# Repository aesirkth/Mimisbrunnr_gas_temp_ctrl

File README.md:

# Mimisbrunnr_gas_temp_ctrl

Mímisbrunnr gas tank temperature control unit

Project hierarchy: Mjölnir → Mimisbrunnr

## About

Mímisbrunnur is a temperature control unit that controls the temperature of the N<sub>2</sub> gas tank that is used as the oxidizer for the Mjölnir rocket.
The unit will regulate the temperature the desired temperature.
It will measure the temperature of the tank and then turn on a pump to allow warm water to flow in a tube around the tank.

## Requirements
1. Regulate the temperature of the oxidizer gas tank for the Mjölnir rocket
2. Manual as well as digital controls
    1. Manual control:
        1. Screen to see configurations
        2. Buttons to control
    2. Digital control:
        1. Connect through wifi and integrated into the system of Mjölnir
        2. Option to connect through CAN bus
3. Measure the temperature
    1. Have 3 temperature sensors: 1 top, 1 middle, 1 bottom
4. Turn a water pump to heat the tank
5. Tolerate rainy, snowy or other similar weather conditions

### Optional Requirements
1. Control heating element
2. Fully Waterproof

## Usage

Buttons to navigate

Connectors

## PCB

## Box

## Software

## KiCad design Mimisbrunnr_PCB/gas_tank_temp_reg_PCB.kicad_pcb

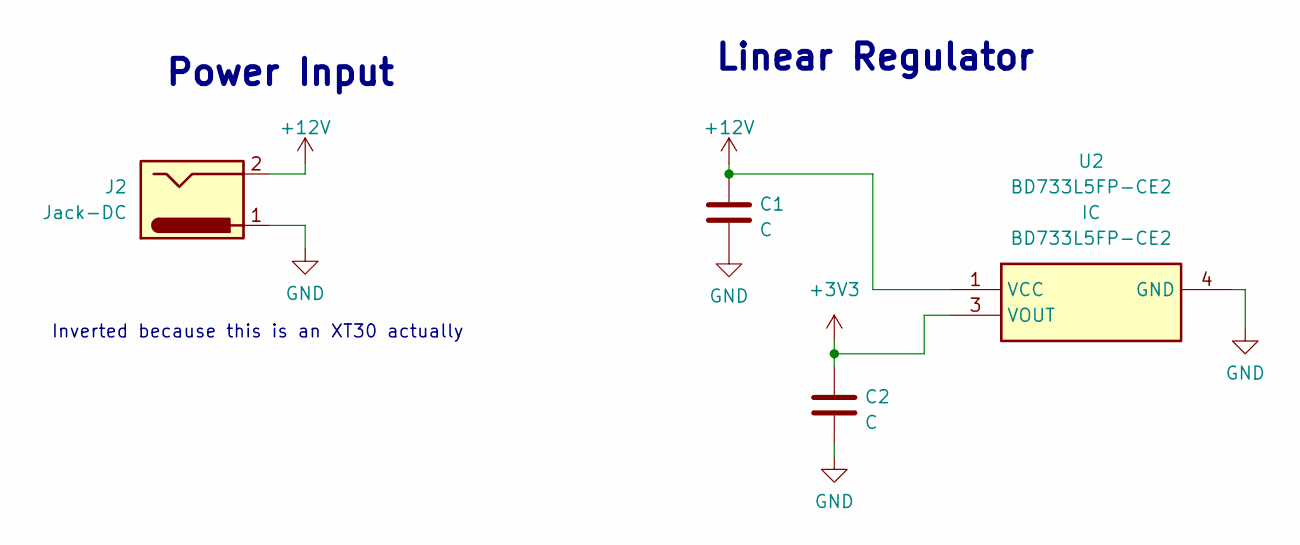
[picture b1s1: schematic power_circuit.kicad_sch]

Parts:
C1, C2: C; C_0805_2012Metric
J2: Jack-DC; AMASS_XT30PW-M_1x02_P2.50mm_Horizontal
U2: BD733L5FP-CE2; BD750L5FPCE2; Mouser Part Number 755-BD733L5FP-CE2

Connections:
+3.3V: C2.1, U2.3 (VOUT); also elsewhere on the board
+12V: C1.1, J2.2, U2.1 (VCC); also elsewhere on the board
GND: C1.2, C2.2, J2.1, U2.4 (GND); also elsewhere on the board

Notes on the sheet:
Power Input
Linear Regulator
Inverted because this is an XT30 actually

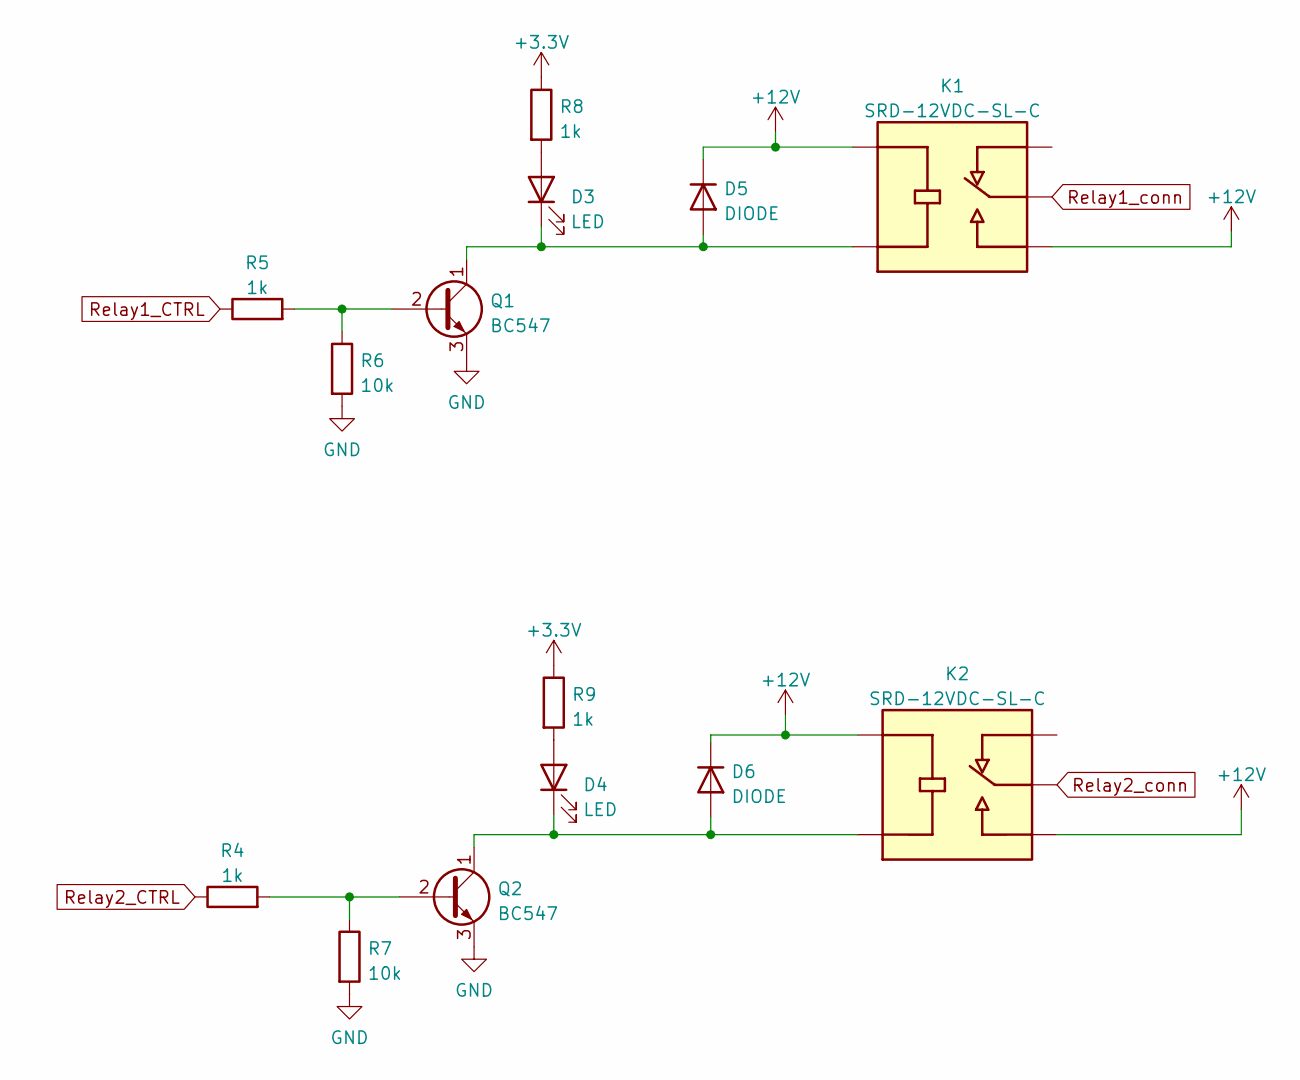
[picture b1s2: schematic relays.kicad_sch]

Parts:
D3, D4: LED; LED_0805_2012Metric
D5, D6: DIODE; D_0805_2012Metric
K1, K2: SRD-12VDC-SL-C; RELAY_SRD-12VDC-SL-C; PARTREV 1.0
Q1, Q2: BC547; TO-92_Inline
R4, R5, R8, R9: 1k; R_0805_2012Metric
R6, R7: 10k; R_0805_2012Metric

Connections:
+3.3V: R8.1, R9.1; also elsewhere on the board
+12V: D5.2 (K), D6.2 (K), K1.COIL1, K1.NO, K2.COIL1, K2.NO; also elsewhere on the board
GND: Q1.3 (E), Q2.3 (E), R6.2, R7.2; also elsewhere on the board
unnamed: D3.1 (K), D5.1 (A), K1.COIL2, Q1.1 (C)
unnamed: D3.2 (A), R8.2
unnamed: D4.1 (K), D6.1 (A), K2.COIL2, Q2.1 (C)
unnamed: D4.2 (A), R9.2
unnamed: Q1.2 (B), R5.2, R6.1
unnamed: Q2.2 (B), R4.2, R7.1
Relay1_CTRL: R5.1; also elsewhere on the board
Relay1_conn: K1.COM; also elsewhere on the board
Relay2_CTRL: R4.1; also elsewhere on the board
Relay2_conn: K2.COM; also elsewhere on the board

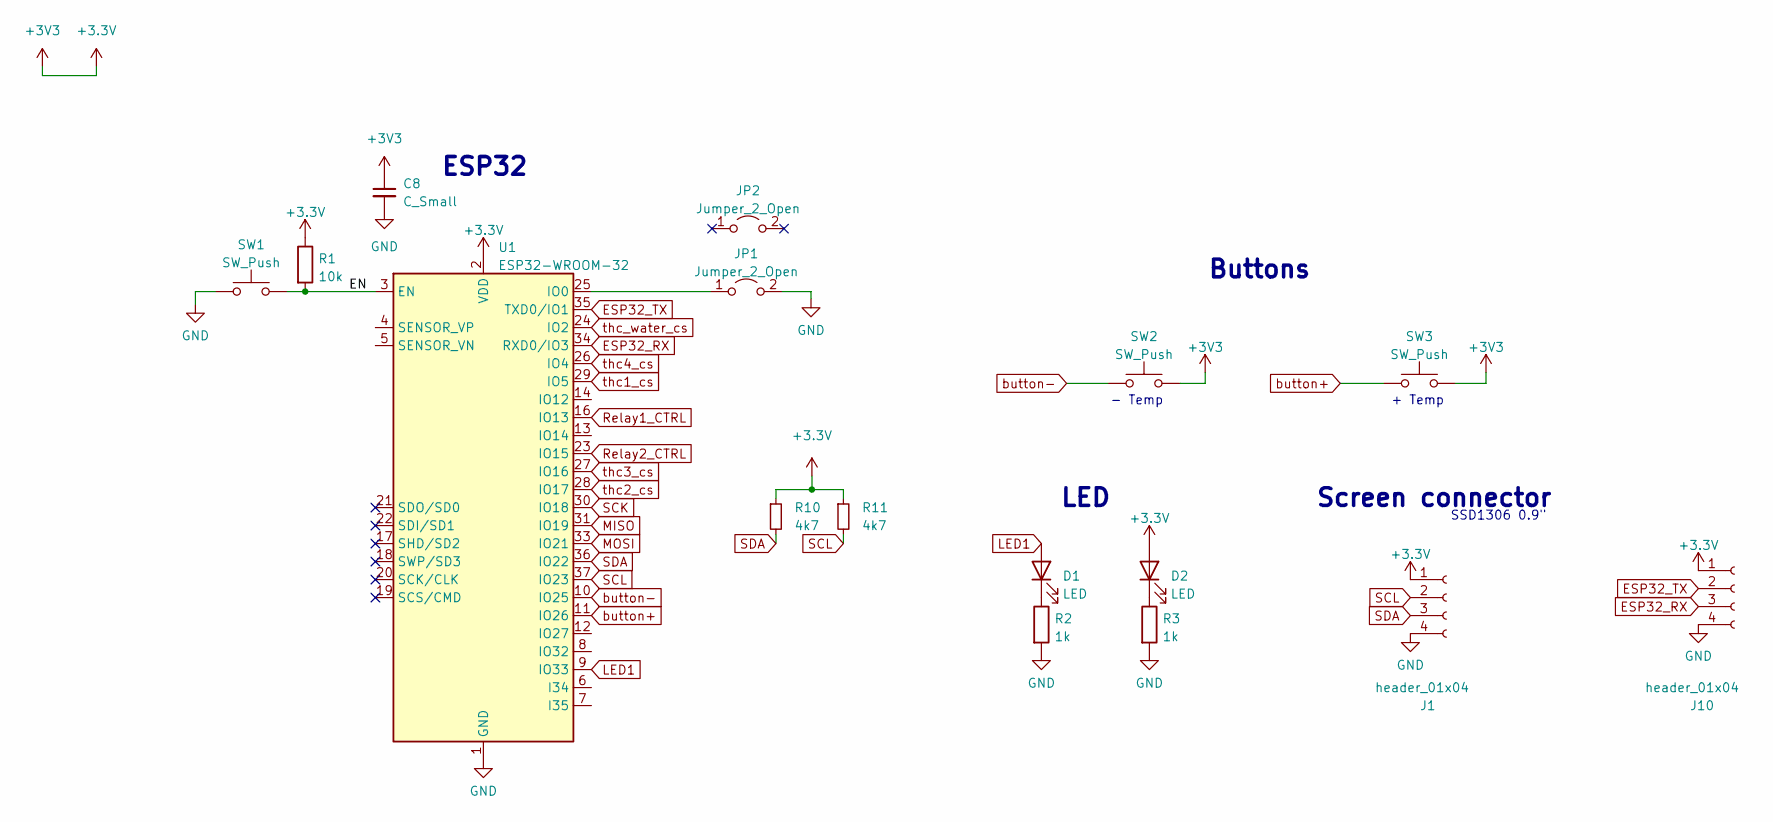
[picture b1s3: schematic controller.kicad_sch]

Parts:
C8: C_Small; C_0805_2012Metric
D1, D2: LED; LED_0805_2012Metric
J1, J10: header_01x04; PinHeader_1x04_P2.54mm_Vertical
JP1, JP2: Jumper_2_Open; PinHeader_1x02_P2.54mm_Vertical
R1: 10k; R_0805_2012Metric
R2, R3: 1k; R_0805_2012Metric
R10, R11: 4k7; R_0805_2012Metric
SW1, SW2, SW3: SW_Push; SW_SPST_B3U-1000P
U1: ESP32-WROOM-32

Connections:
+3.3V: C8.1, D2.2 (A), J1.1, J10.1, R1.1, R10.1, R11.1, SW2.2, SW3.2, U1.2 (VDD); also elsewhere on the board
/Controller/EN: R1.2, SW1.2, U1.3 (EN)
ESP32_RX: J10.3, U1.34 (RXD0/IO3)
ESP32_TX: J10.2, U1.35 (TXD0/IO1)
GND: C8.2, J1.4, J10.4, JP1.2 (B), R2.2, R3.2, SW1.1, U1.1 (GND), U1.15 (GND), U1.38 (GND), U1.39 (GND); also elsewhere on the board
LED1: D1.2 (A), U1.9 (IO33)
MISO: U1.31 (IO19); also elsewhere on the board
MOSI: U1.33 (IO21); also elsewhere on the board
unnamed: D1.1 (K), R2.1
unnamed: D2.1 (K), R3.1
unnamed: JP1.1 (A), U1.25 (IO0)
Relay1_CTRL: U1.16 (IO13); also elsewhere on the board
Relay2_CTRL: U1.23 (IO15); also elsewhere on the board
SCK: U1.30 (IO18); also elsewhere on the board
SCL: J1.2, R11.2, U1.37 (IO23)
SDA: J1.3, R10.2, U1.36 (IO22)
button+: SW3.1, U1.11 (IO26)
button-: SW2.1, U1.10 (IO25)
thc1_cs: U1.29 (IO5); also elsewhere on the board
thc2_cs: U1.28 (IO17); also elsewhere on the board
thc3_cs: U1.27 (IO16); also elsewhere on the board
thc4_cs: U1.26 (IO4); also elsewhere on the board
thc_water_cs: U1.24 (IO2); also elsewhere on the board

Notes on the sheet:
Buttons
Screen connector
+ Temp
ESP32
- Temp
LED
SSD1306 0.9"

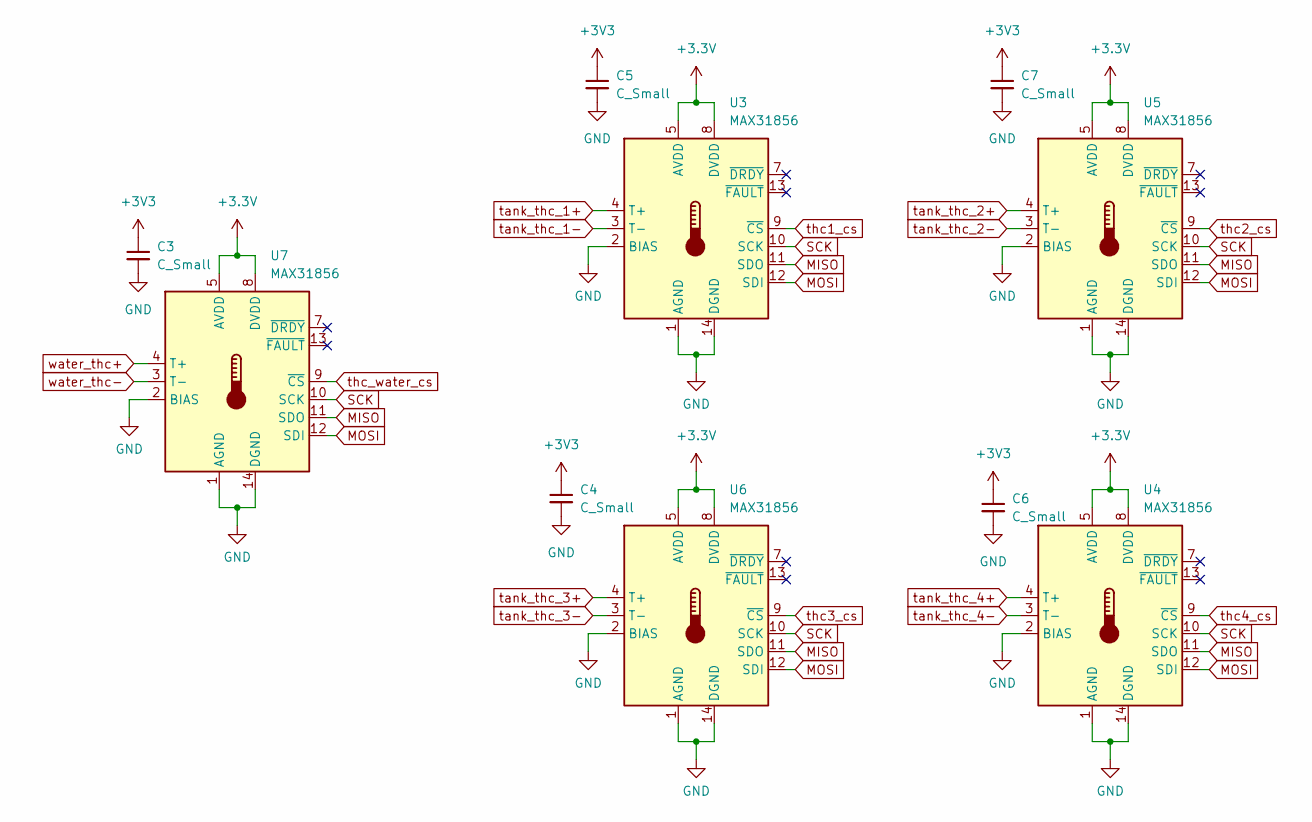
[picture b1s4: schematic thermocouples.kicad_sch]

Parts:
C3, C4, C5, C6, C7: C_Small; C_0805_2012Metric
U3, U4, U5, U6, U7: MAX31856; TSSOP-14_4.4x5mm_P0.65mm

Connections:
+3.3V: C3.1, C4.1, C5.1, C6.1, C7.1, U3.5 (AVDD), U3.8 (DVDD), U4.5 (AVDD), U4.8 (DVDD), U5.5 (AVDD), U5.8 (DVDD), U6.5 (AVDD), U6.8 (DVDD), U7.5 (AVDD), U7.8 (DVDD); also elsewhere on the board
GND: C3.2, C4.2, C5.2, C6.2, C7.2, U3.1 (AGND), U3.2 (BIAS), U3.14 (DGND), U4.1 (AGND), U4.2 (BIAS), U4.14 (DGND), U5.1 (AGND), U5.2 (BIAS), U5.14 (DGND), U6.1 (AGND), U6.2 (BIAS), U6.14 (DGND), U7.1 (AGND), U7.2 (BIAS), U7.14 (DGND); also elsewhere on the board
MISO: U3.11 (SDO), U4.11 (SDO), U5.11 (SDO), U6.11 (SDO), U7.11 (SDO); also elsewhere on the board
MOSI: U3.12 (SDI), U4.12 (SDI), U5.12 (SDI), U6.12 (SDI), U7.12 (SDI); also elsewhere on the board
SCK: U3.10 (SCK), U4.10 (SCK), U5.10 (SCK), U6.10 (SCK), U7.10 (SCK); also elsewhere on the board
tank_thc_1+: U3.4 (T+); also elsewhere on the board
tank_thc_1-: U3.3 (T-); also elsewhere on the board
tank_thc_2+: U5.4 (T+); also elsewhere on the board
tank_thc_2-: U5.3 (T-); also elsewhere on the board
tank_thc_3+: U6.4 (T+); also elsewhere on the board
tank_thc_3-: U6.3 (T-); also elsewhere on the board
tank_thc_4+: U4.4 (T+); also elsewhere on the board
tank_thc_4-: U4.3 (T-); also elsewhere on the board
thc1_cs: U3.9 (~CS); also elsewhere on the board
thc2_cs: U5.9 (~CS); also elsewhere on the board
thc3_cs: U6.9 (~CS); also elsewhere on the board
thc4_cs: U4.9 (~CS); also elsewhere on the board
thc_water_cs: U7.9 (~CS); also elsewhere on the board
water_thc+: U7.4 (T+); also elsewhere on the board
water_thc-: U7.3 (T-); also elsewhere on the board

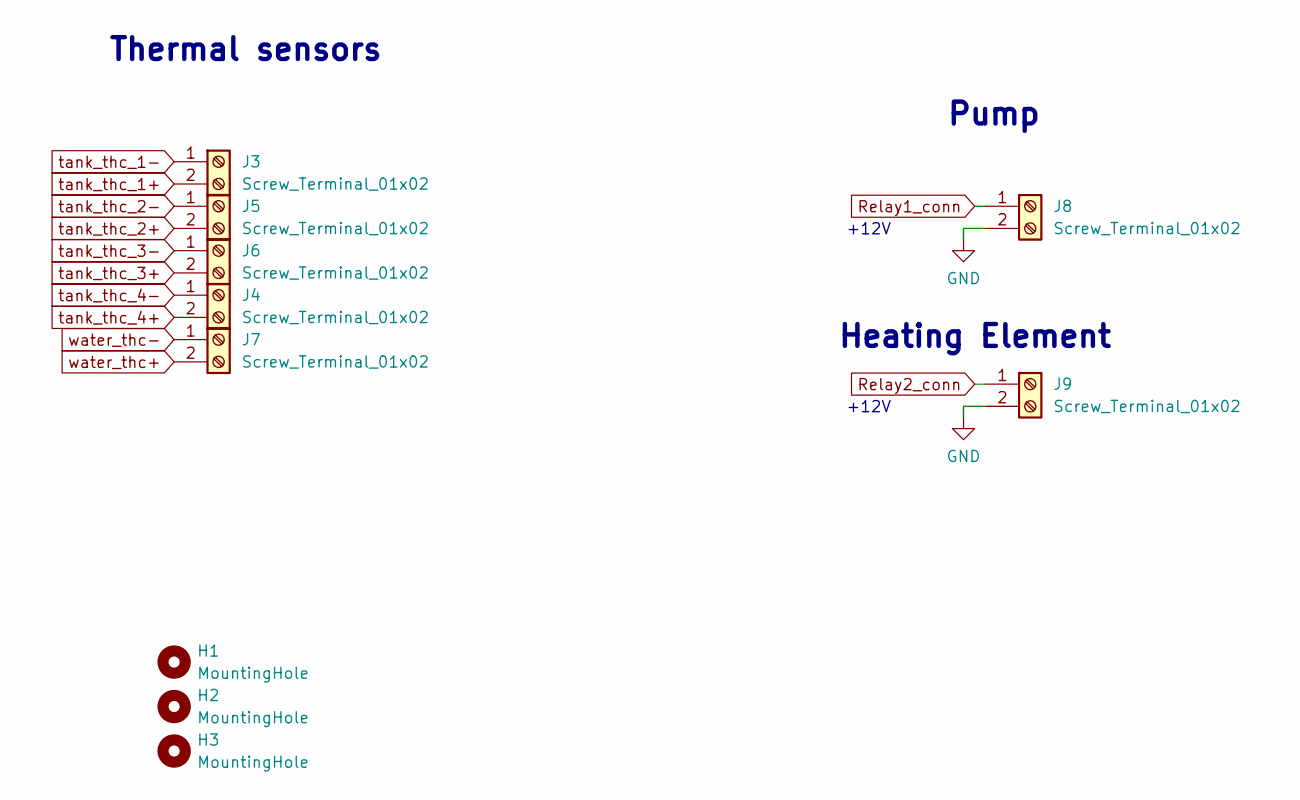
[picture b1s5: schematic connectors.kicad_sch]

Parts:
H1, H2, H3: MountingHole; MountingHole_3.2mm_M3
J3, J4, J5, J6, J7, J8, J9: Screw_Terminal_01x02; TerminalBlock_TE_282834-2_1x02_P2.54mm_Horizontal

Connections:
GND: J8.2, J9.2; also elsewhere on the board
Relay1_conn: J8.1; also elsewhere on the board
Relay2_conn: J9.1; also elsewhere on the board
tank_thc_1+: J3.2; also elsewhere on the board
tank_thc_1-: J3.1; also elsewhere on the board
tank_thc_2+: J5.2; also elsewhere on the board
tank_thc_2-: J5.1; also elsewhere on the board
tank_thc_3+: J6.2; also elsewhere on the board
tank_thc_3-: J6.1; also elsewhere on the board
tank_thc_4+: J4.2; also elsewhere on the board
tank_thc_4-: J4.1; also elsewhere on the board
water_thc+: J7.2; also elsewhere on the board
water_thc-: J7.1; also elsewhere on the board

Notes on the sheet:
Heating Element
+12V
Pump
Thermal sensors

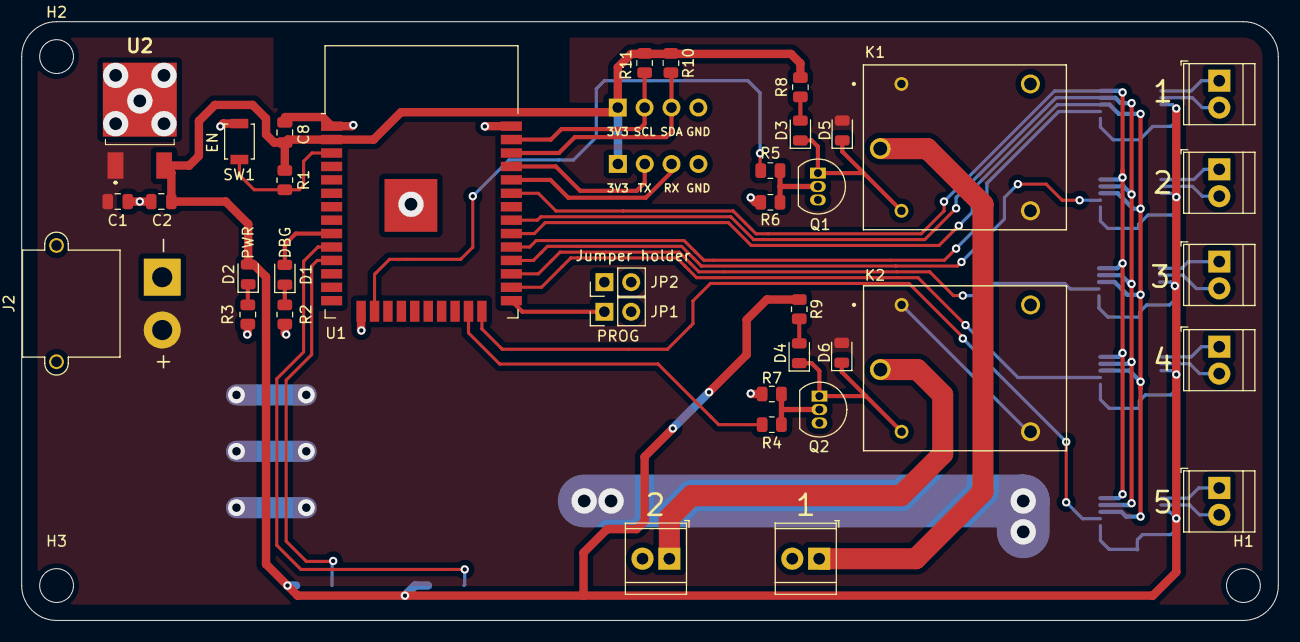
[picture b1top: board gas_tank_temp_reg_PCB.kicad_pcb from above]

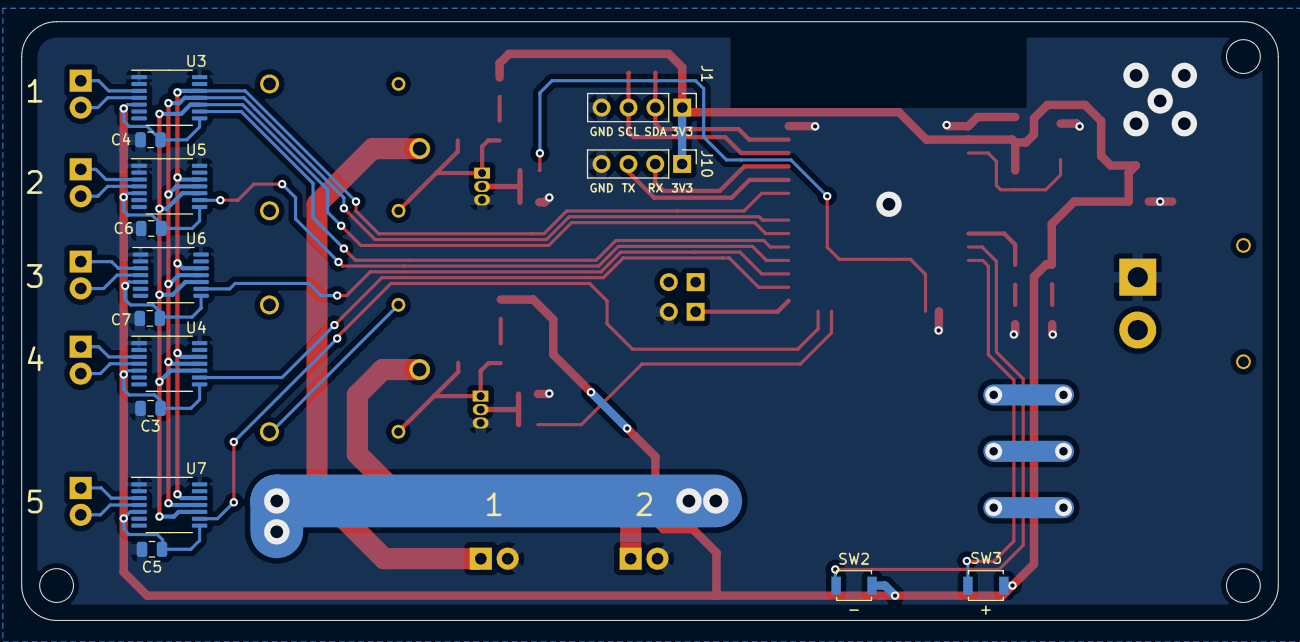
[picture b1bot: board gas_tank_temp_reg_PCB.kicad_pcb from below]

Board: 2 copper layers, 118.9 x 56.6 mm, 54 parts (14 on the bottom side), 42 nets.

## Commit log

2022-11-08 Init commit / Adding PCB project
2022-12-09 Adding requirements to README.md
2022-12-09 Adding firmware to project. Some groundwork for the FW has been done
2022-12-09 Adding more requirements to README
2023-04-16 finalize schematic
2023-05-09 routing finished
2023-05-09 Improve style
2023-05-09 add missing files oops
